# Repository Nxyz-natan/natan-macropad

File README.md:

# Natan's Macropad Take Your Heart

A 16-key Persona 5 themed macropad with RGB LEDs, OLED display, and sandwich mount case. Built as part of the Hack Club Blueprint/Hackpad program.

## Features
- 16 keys in a 4×4 matrix
- 32x SK6812MINI-E RGB LEDs between switches
- 0.91" 128x32 OLED display showing Joker silhouette on boot
- Sandwich mount case with engraved "TAKE YOUR HEART" and "Natan" text
- KMK firmware on Seeed XIAO RP2040

## CAD Model
Designed in Shapr3D. Sandwich mount style with a plate on top and case bottom. The plate has switch cutouts, RGB holes, and an OLED window. The case has a USB-C cutout on the side and engraved Persona 5 text on the walls. Held together with 4x M3x16mm screws.

## PCB
Made in KiCad. The silkscreen features the Phantom Thieves logo and "TAKE YOUR HEART" text imported from an SVG. 2 layer board, 99.3x95.9mm.

### Schematic

### PCB

## Firmware Overview
This macropad uses KMK firmware running on CircuitPython.

- 16 keys mapped to productivity shortcuts and mouse controls
- RGB LEDs with rainbow effect
- OLED displays a Joker silhouette on boot

### Keymap
| Position | Action |
|----------|--------|
| 1 | Sleep |
| 2 | Undo |
| 3 | Find |
| 4 | Mute |
| 5 | Copy |
| 6 | Paste |
| 7 | Select All |
| 8 | F3 |
| 9 | Mouse Wheel Up |
| 10 | Right Click |
| 11 | Up Arrow |
| 12 | F5 |
| 13 | Mouse Wheel Down |
| 14 | Left Arrow |
| 15 | Down Arrow |
| 16 | Right Arrow |

## BOM
Here's everything you need to build this macropad:

- 16x Cherry MX Switches
- 32x SK6812MINI-E RGB LEDs
- 16x 1N4148 Diodes
- 1x 0.91" 128x32 OLED Display
- 1x Seeed XIAO RP2040
- 4x M3x16mm Screws
- 1x PCB (2 layer, 99.3x95.9mm)
- 1x 3D Printed Case (plate + bottom)

## Extra Stuff
Persona 5 is one of my favourite games so I had to make a macropad themed around it. The Phantom Thieves logo on the PCB silkscreen came out way better than I expected. Can't wait to build it!

*Made by Natan Hack Club Blueprint 2026*

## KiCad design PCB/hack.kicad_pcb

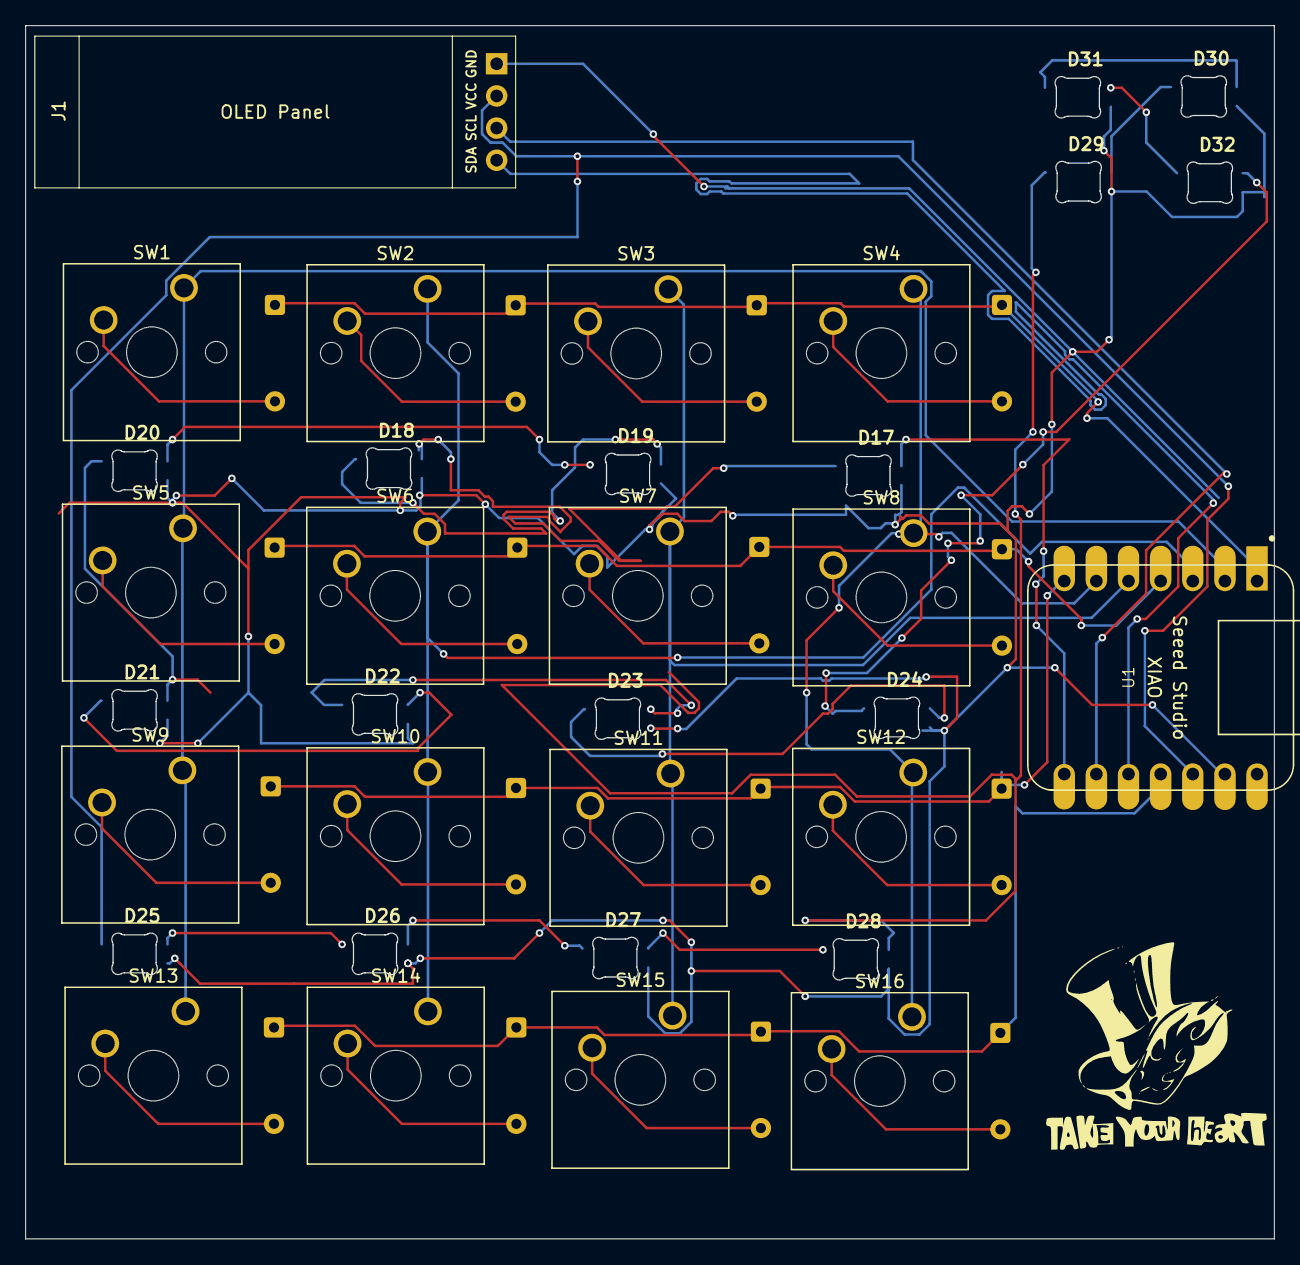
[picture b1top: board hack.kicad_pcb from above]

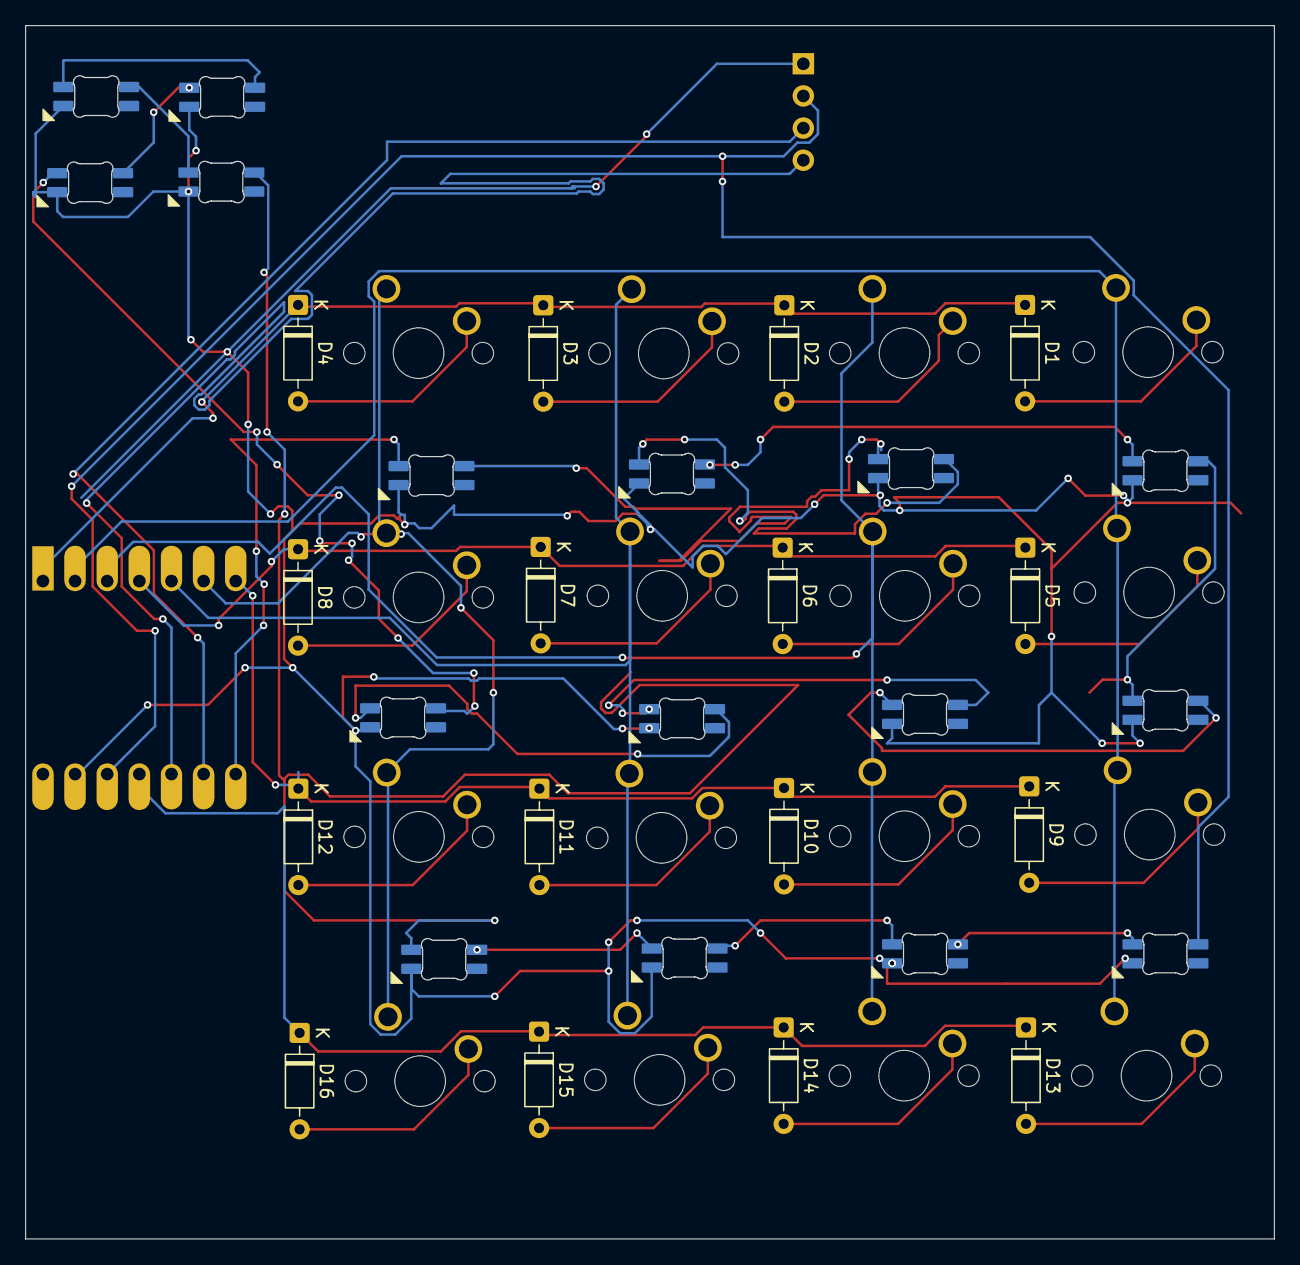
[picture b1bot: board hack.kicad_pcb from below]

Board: 2 copper layers, 98.6 x 95.8 mm, 50 parts (16 on the bottom side), 44 nets.

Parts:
D1, D2, D3, D4, D5, D6, D7, D8, D9, D10, D11, D12, D13, D14, D15, D16: 1N4148; D_DO-35_SOD27_P7.62mm_Horizontal
D17, D18, D19, D20, D21, D22, D23, D24, D25, D26, D27, D28, D29, D30, D31, D32: SK6812MINI-E; SK6812MINI-E_fixed
J1: Conn_01x04_Pin; SSD1306-0.91-OLED-4pin-128x32
SW1, SW2, SW3, SW4, SW5, SW6, SW7, SW8, SW9, SW10, SW11, SW12, SW13, SW14, SW15, SW16: SW_Push; SW_Cherry_MX_1.00u_PCB
U1: MOUDLE-SEEEDUINO-XIAO; XIAO-Generic-Hybrid-14P-2.54-21X17.8MM

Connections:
GND: D17.3 (VSS), D18.3 (VSS), D19.3 (VSS), D20.3 (VSS), D21.3 (VSS), D22.3 (VSS), D23.3 (VSS), D24.3 (VSS), D25.3 (VSS), D26.3 (VSS), D27.3 (VSS), D28.3 (VSS), D29.3 (VSS), D30.3 (VSS), D31.3 (VSS), D32.3 (VSS), J1.1, U1.13 (GND)
LED_DATA: D17.4 (DIN), U1.8 (PB09_A7_D7_RX)
unnamed: D1.2 (A), SW1.2
unnamed: D2.2 (A), SW2.2
unnamed: D3.2 (A), SW3.2
unnamed: D4.2 (A), SW4.2
unnamed: D5.2 (A), SW5.2
unnamed: D6.2 (A), SW6.2
unnamed: D7.2 (A), SW7.2
unnamed: D8.2 (A), SW8.2
unnamed: D9.2 (A), SW9.2
unnamed: D10.2 (A), SW10.2
unnamed: D11.2 (A), SW11.2
unnamed: D12.2 (A), SW12.2
unnamed: D13.2 (A), SW13.2
unnamed: D14.2 (A), SW14.2
unnamed: D15.2 (A), SW15.2
unnamed: D16.2 (A), SW16.2
unnamed: D17.1 (DOUT), D18.4 (DIN)
unnamed: D18.1 (DOUT), D19.4 (DIN)
unnamed: D19.1 (DOUT), D20.4 (DIN)
unnamed: D20.1 (DOUT), D21.4 (DIN)
unnamed: D21.1 (DOUT), D22.4 (DIN)
unnamed: D22.1 (DOUT), D23.4 (DIN)
unnamed: D23.1 (DOUT), D24.4 (DIN)
unnamed: D24.1 (DOUT), D32.4 (DIN)
unnamed: D25.4 (DIN), D26.1 (DOUT)
unnamed: D26.4 (DIN), D27.1 (DOUT)
unnamed: D27.4 (DIN), D28.1 (DOUT)
unnamed: D28.4 (DIN), D29.1 (DOUT)
unnamed: D29.4 (DIN), D30.1 (DOUT)
unnamed: D30.4 (DIN), D31.1 (DOUT)
unnamed: D31.4 (DIN), D32.1 (DOUT)
unnamed: J1.3, U1.9 (PA7_A8_D8_SCK)
unnamed: J1.4, U1.10 (PA5_A9_D9_MISO)
VCC: D25.1 (VDD), J1.2, U1.12 (3V3)
column 0: SW1.1, SW5.1, SW9.1, SW13.1, U1.2 (PA4_A1_D1)
column 1: SW2.1, SW6.1, SW10.1, SW14.1, U1.3 (PA10_A2_D2)
column 2: SW3.1, SW7.1, SW11.1, SW15.1, U1.5 (PA8_A4_D4_SDA)
column 3: SW4.1, SW8.1, SW12.1, SW16.1, U1.6 (PA9_A5_D5_SCL)
row 0: D1.1 (K), D2.1 (K), D3.1 (K), D4.1 (K), U1.1 (PA02_A0_D0)
row 1: D5.1 (K), D6.1 (K), D7.1 (K), D8.1 (K), U1.4 (PA11_A3_D3)
row 2: D9.1 (K), D10.1 (K), D11.1 (K), D12.1 (K), U1.7 (PB08_A6_D6_TX)
row 3: D13.1 (K), D14.1 (K), D15.1 (K), D16.1 (K), U1.11 (PA6_A10_D10_MOSI)

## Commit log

2026-03-28 Add project files
2026-03-28 Add README and screenshots
2026-03-31 README.md
